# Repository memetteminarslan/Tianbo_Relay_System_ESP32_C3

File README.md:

# Tianbo_Relay_System_LORA_ESP32_C3
Ana Özellikler:

Uzun Menzilli Kablosuz İletişim: ESP32-C3 mikrodenetleyici, düşük güç tüketimi ve uzun menzil avantajlarına sahip olan LoRa (Long Range) iletişim protokolünü benimser. Bu sayede, kontrol kutusu ve kontrol edilecek cihazlar arasında stabil ve güvenilir bir iletişim kurulur.

Esnek ve Güçlü Mikrodenetleyici: ESP32-C3, entegre Wi-Fi ve Bluetooth özellikleriyle donatılmış, güçlü ve esnek bir mikrodenetleyicidir. Bu sayede, kutuda birden fazla cihazı kontrol etmek ve yönetmek için yeterli işlem gücü ve kaynak sağlar.

Düşük Güç Tüketimi: Proje, pil ile çalışabilme yeteneğine odaklanarak düşük güç tüketimli bir tasarım sunar. LoRa teknolojisi,  enerji verimliliği sayesinde uzun pil ömrü sağlar.

Kolay Kurulum ve Kullanım: Uzaktan kontrol kutusu, kullanıcı dostu arayüzü sayesinde kolay kurulum ve kullanım sağlar. Mobil uygulamalar veya web tabanlı arayüzler aracılığıyla cihazların durumunu takip etmek ve kontrol etmek oldukça basittir.

Güvenlik Odaklı Tasarım: Proje, iletişimde kullanılan LoRa protokolünü şifreleme ve güvenlik önlemleriyle destekleyerek güvenli bir uzaktan kontrol imkanı sunar. Kimlik doğrulama ve veri bütünlüğü gibi güvenlik önlemleri, yetkisiz erişimleri engeller.

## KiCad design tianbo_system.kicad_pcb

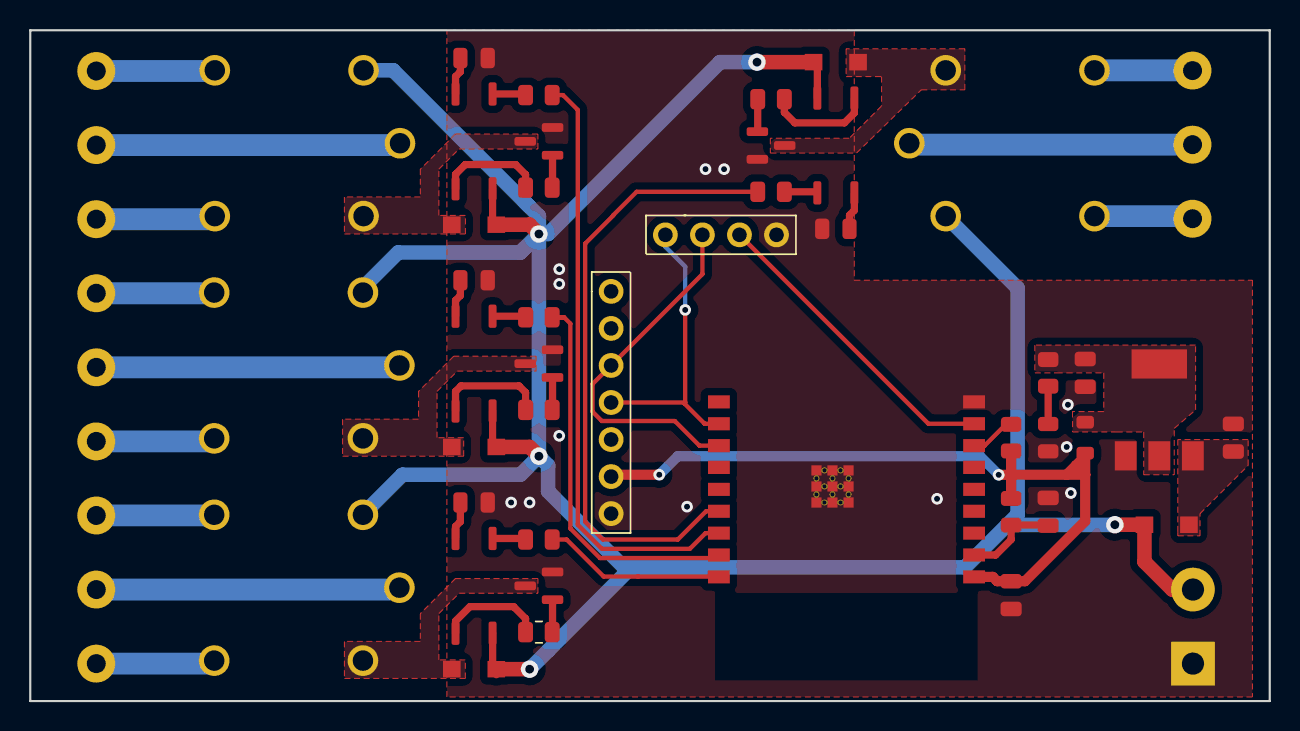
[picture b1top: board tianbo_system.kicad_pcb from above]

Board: 2 copper layers, 85.0 x 46.0 mm, 45 parts (0 on the bottom side), 47 nets.

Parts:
C1, C2: C; C_0805_2012Metric
C3: 1uF; C_0805_2012Metric
C4: 0.1uF; C_0805_2012Metric
D1, D2, D3, D4, D5: LED; LED_0805_2012Metric
D6, D7, D8, D9, D10: 1N5819W; SODFL3618X110N
FB1: FerriteBead_Small; L_0805_2012Metric
J1: Conn_01x04_Male; PinSocket_1x04_P2.54mm_Vertical
J2: Screw_Terminal_01x02; TerminalBlock_bornier-2_P5.08mm
J3: Screw_Terminal_01x03; TerminalBlock_bornier-3_P5.08mm
J4: Screw_Terminal_01x09; TerminalBlock_Phoenix_PT-1,5-9-5.0-H_1x09_P5.00mm_Horizontal
J5: Conn_01x07_Pin; PinHeader_1x07_P2.54mm_Vertical
K1, K2, K3, K4: HJR-78F__TRKM_; HJR78FTRKM
Q1, Q2, Q3, Q4: BC817; SOT-23
R1: 10k; R_0805_2012Metric
R2: R; R_0805_2012Metric
R3: 10K; R_0805_2012Metric
R4, R5, R6, R7: 220r; R_0805_2012Metric
R8, R9, R10, R11: 1k; R_0805_2012Metric
U1: ESP32-C3-WROOM-02-N4; MODULE_ESP32-C3-WROOM-02-H4
U2: AMS1117-3.3; SOT-223-3_TabPin2
U3, U4, U5, U6: TLP185; SOIC-4_4.55x3.7mm_P2.54mm

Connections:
+3V3: C4.1, FB1.2, J5.6, R1.1, R3.1, U1.1 (3V3)
+5V: D6.1 (K), D7.1 (K), D8.1 (K), D9.1 (K), D10.2 (A), J2.2, K1.1 (COIL_1), K2.1 (COIL_1), K3.1 (COIL_1), K4.1 (COIL_1), U3.6, U4.6, U5.6, U6.6
EN: C3.1, R3.2, U1.2 (EN)
GND: C1.2, C2.2, C3.2, C4.2, D1.1 (K), D2.1 (K), D3.1 (K), D4.1 (K), D5.1 (K), J1.4, J2.1, J5.7, Q1.2 (E), Q2.2 (E), Q3.2 (E), Q4.2 (E), U1.9 (GND), U1.19 (GND), U1.20 (GND), U1.21 (GND), U1.22 (GND), U1.23 (GND), U1.24 (GND), U1.25 (GND), U1.26 (GND), U1.27 (GND), U1.28 (GND), U1.29 (GND), U1.30 (GND), U1.31 (GND), U1.32 (GND), U1.33 (GND), U1.34 (GND), U1.35 (GND), U1.36 (GND), U1.37 (GND), U1.38 (GND), U1.39 (GND), U2.1 (GND)
IO8: R1.2, U1.7 (IO8)
IO9: J1.3, U1.8 (IO9)
unnamed: D1.2 (A), R2.2
unnamed: D2.2 (A), U3.3
unnamed: D3.2 (A), U4.3
unnamed: D4.2 (A), U5.3
unnamed: D5.2 (A), U6.3
unnamed: D6.2 (A), K1.4 (COIL_2), Q1.3 (C)
unnamed: D7.2 (A), K2.4 (COIL_2), Q2.3 (C)
unnamed: D8.2 (A), K3.4 (COIL_2), Q3.3 (C)
unnamed: D9.2 (A), K4.4 (COIL_2), Q4.3 (C)
unnamed: C1.1, D10.1 (K), U2.3 (VI)
unnamed: J3.1, K4.3 (NC)
unnamed: J3.2, K4.5 (COM)
unnamed: J3.3, K4.2 (NO)
unnamed: J4.1, K1.3 (NC)
unnamed: J4.2, K1.5 (COM)
unnamed: J4.3, K1.2 (NO)
unnamed: J4.4, K2.3 (NC)
unnamed: J4.5, K2.5 (COM)
unnamed: J4.6, K2.2 (NO)
unnamed: J4.7, K3.3 (NC)
unnamed: J4.8, K3.5 (COM)
unnamed: J4.9, K3.2 (NO)
unnamed: Q1.1 (B), R8.2
unnamed: Q2.1 (B), R9.2
unnamed: Q3.1 (B), R10.2
unnamed: Q4.1 (B), R11.2
unnamed: R4.2, U3.1
unnamed: R5.2, U4.1
unnamed: R6.2, U5.1
unnamed: R7.2, U6.1
unnamed: R8.1, U3.4
unnamed: R9.1, U4.4
unnamed: R10.1, U5.4
unnamed: R11.1, U6.4
unnamed: C2.1, FB1.1, R2.1, U2.2 (VO)
RLY01: R4.1, U1.18 (IO0)
RLY02: R5.1, U1.17 (IO1)
RLY03: R6.1, U1.16 (IO2)
RLY04: R7.1, U1.15 (IO3)
RX: J1.1, J5.4, U1.11 (RXD)
TX: J1.2, J5.3, U1.12 (TXD)
